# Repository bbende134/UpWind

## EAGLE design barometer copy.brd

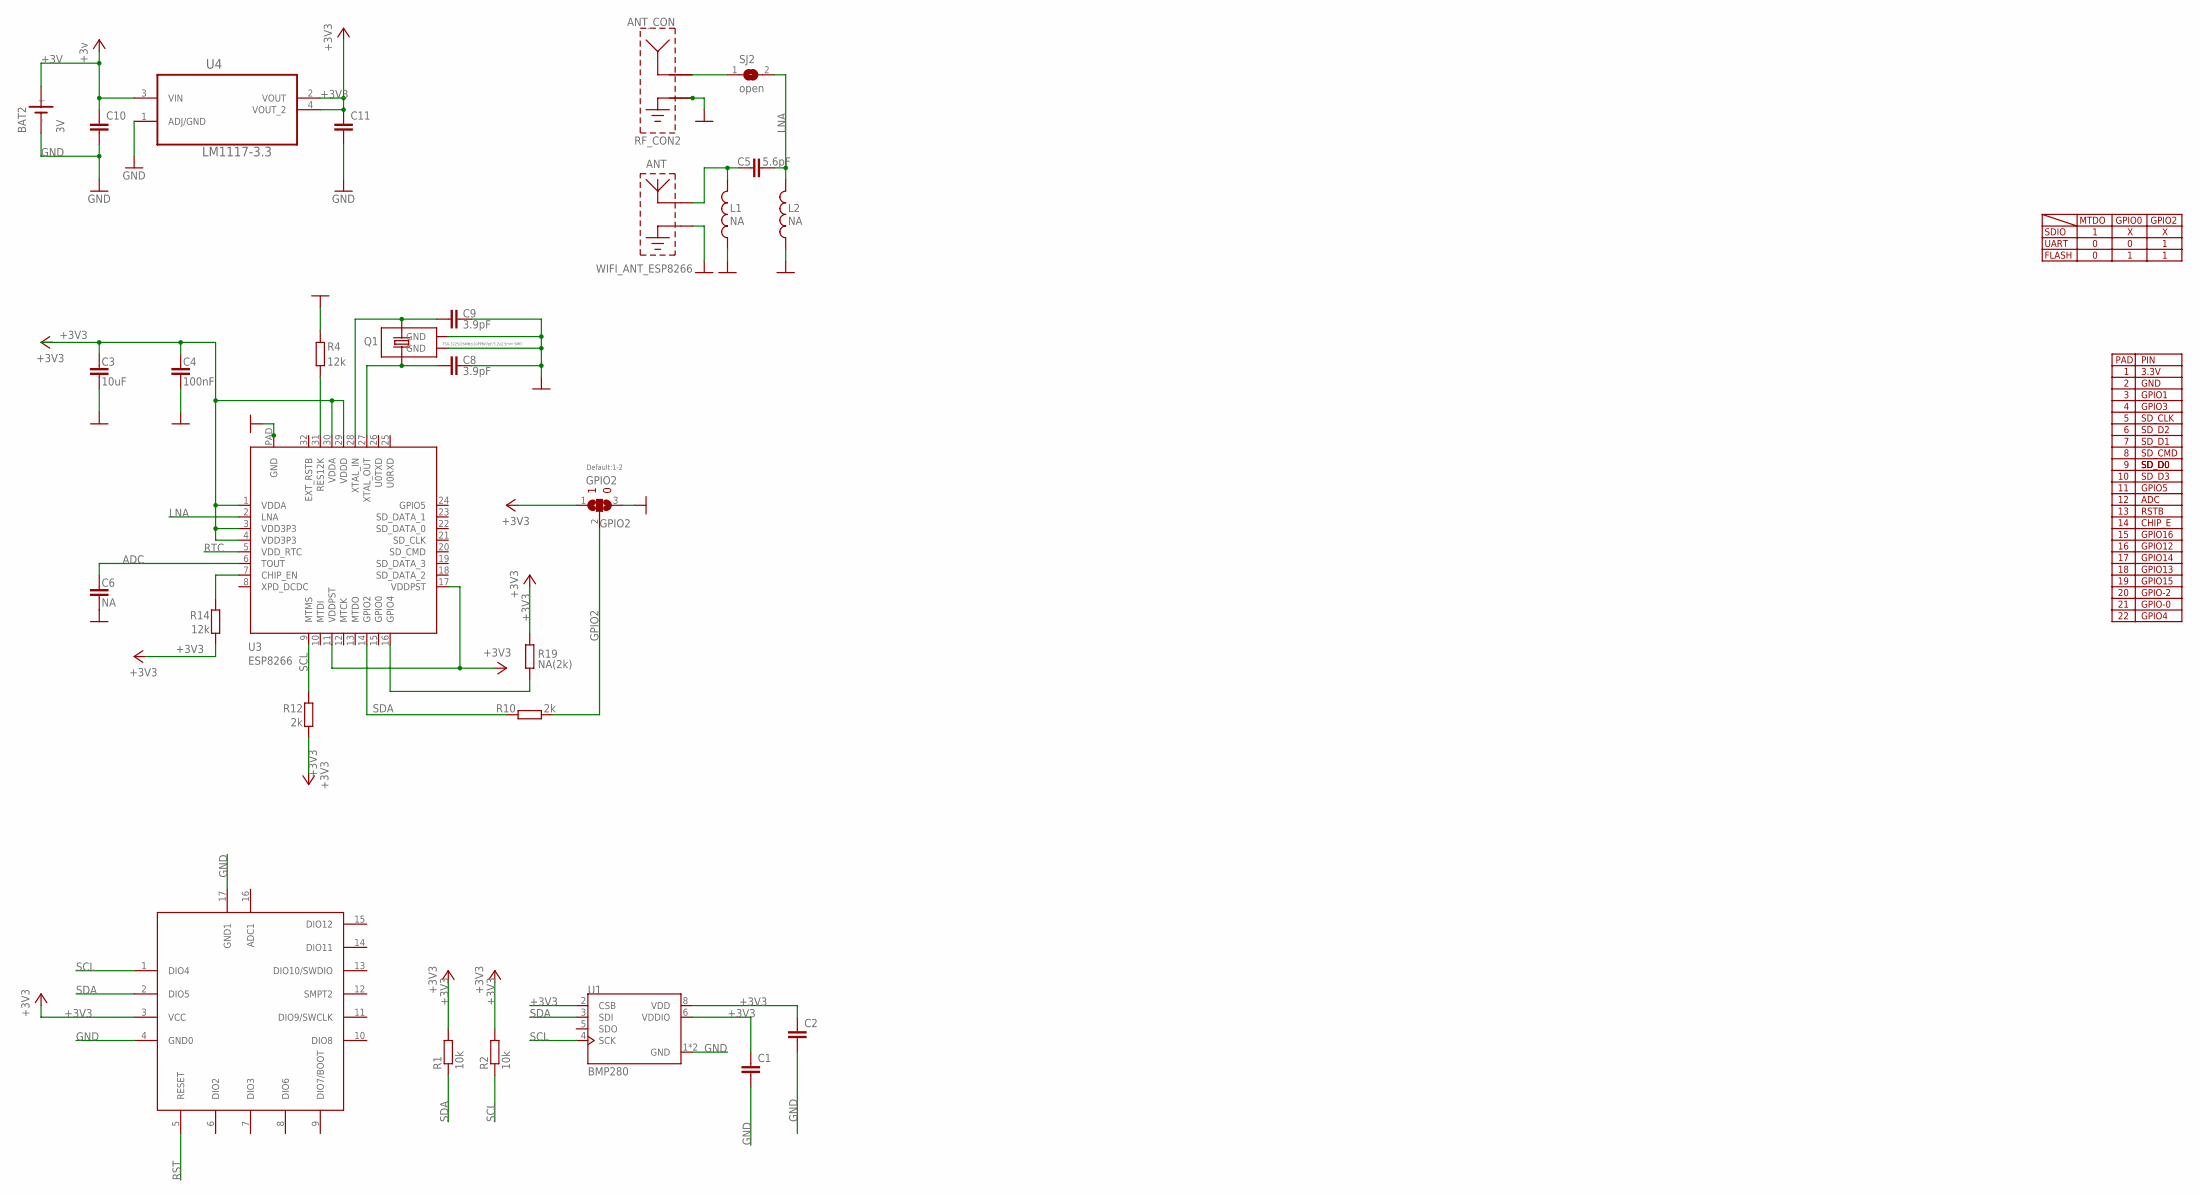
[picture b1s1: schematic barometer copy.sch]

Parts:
ANT: WIFI_ANT_ESP8266; ESP8266_ANT
ANT_CON: RF_CON2; RF_CONNECTOR_I-PEX_NO_CREAM
BAT2: 3V; SN2032
C1, C2, C10: 47u; C1206
C3: 10uF; C0603_DWS
C4: 100nF; C0402_TI
C5: 5.6pF; C0402_TI
C6: NA; C0402_TI
C8, C9: 3.9pF; C0402_TI
C11: 10u; C1206
GPIO2: Default:1-2; SJ_2_SMALLER
L1, L2: NA; L0402_TI
Q1: TSX-3225/26MHz/10PPM/7pF/3.2x2.5mm SMD; NX3225SA
R1, R2: 10k; R0402
R4, R14: 12k; R0402_TI
R10, R12: 2k; R0402_TI
R19: NA(2k); R0402_TI
SJ2: open; SJ_1_SMALLER
U1: BMP280; XDCR_BMP280
U3: ESP8266; QFN32_PAD
U4: LM1117-3.3; SOT230
U$1: BLUENRG-234BLEMODULE

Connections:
+3V: BAT2.+, C10.1, U4.3 (VIN)
+3V3: C1.1, C2.1, C3.1, C4.1, C11.1, GPIO2.1, R1.2, R2.2, R12.2, R14.2, R19.1, U1.2 (CSB), U1.6 (VDDIO), U1.8 (VDD), U3.1 (VDDA), U3.3 (VDD3P3), U3.4 (VDD3P3), U3.11 (VDDPST), U3.17 (VDDPST), U3.29 (VDDD), U3.30 (VDDA), U4.2 (VOUT), U4.4 (VOUT_2), U$1.3 (VCC)
ADC: C6.1, U3.6 (TOUT)
GND: ANT.GND, ANT_CON.1 (GND_1), ANT_CON.2 (GND_2), BAT2.-, C1.2, C2.2, C3.2, C4.2, C6.2, C8.1, C9.1, C10.2, C11.2, GPIO2.3, L1.1, L2.1, Q1.NC_1 (GND), Q1.NC_2 (GND), R4.2, U1.1 (GND), U1.7 (GND), U3.P$1 (GND), U3.P$2 (GND), U3.P$3 (GND), U3.P$4 (GND), U3.P$5 (GND), U3.P$6 (GND), U3.P$7 (GND), U3.P$8 (GND), U3.P$9 (GND), U3.PAD (GND), U4.1 (ADJ/GND), U$1.4 (GND0), U$1.17 (GND1)
GPIO2: GPIO2.2, R10.1
GPIO4: R19.2, U3.16 (GPIO4)
LNA: C5.2, L2.2, SJ2.2, U3.2 (LNA)
unnamed: ANT_CON.ANT, SJ2.1
unnamed: R14.1, U3.7 (CHIP_EN)
unnamed: ANT.ANT, C5.1, L1.2
unnamed: C8.2, Q1.2, U3.27 (XTAL_OUT)
unnamed: R4.1, U3.31 (RES12K)
unnamed: C9.2, Q1.1, U3.28 (XTAL_IN)
RST: U$1.5 (RESET)
RTC: U3.5 (VDD_RTC)
SCL: R2.1, R12.1, U1.4 (SCK), U3.9 (MTMS), U$1.1 (DIO4)
SDA: R1.1, R10.2, U1.3 (SDI), U3.14 (GPIO2), U$1.2 (DIO5)

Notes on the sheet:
SDIO
UART
FLASH
MTDO
GPIO0
GPIO2
PAD
GPIO1
GPIO3
SD_CLK
SD_D0
SD_D1
SD_D2
SD_D3
SD_CMD
3.3V
GND
GPIO5
GPIO4
GPIO-0
GPIO-2
GPIO15
GPIO13
GPIO12
GPIO14
GPIO16
ADC
PIN
RSTB
CHIP_E

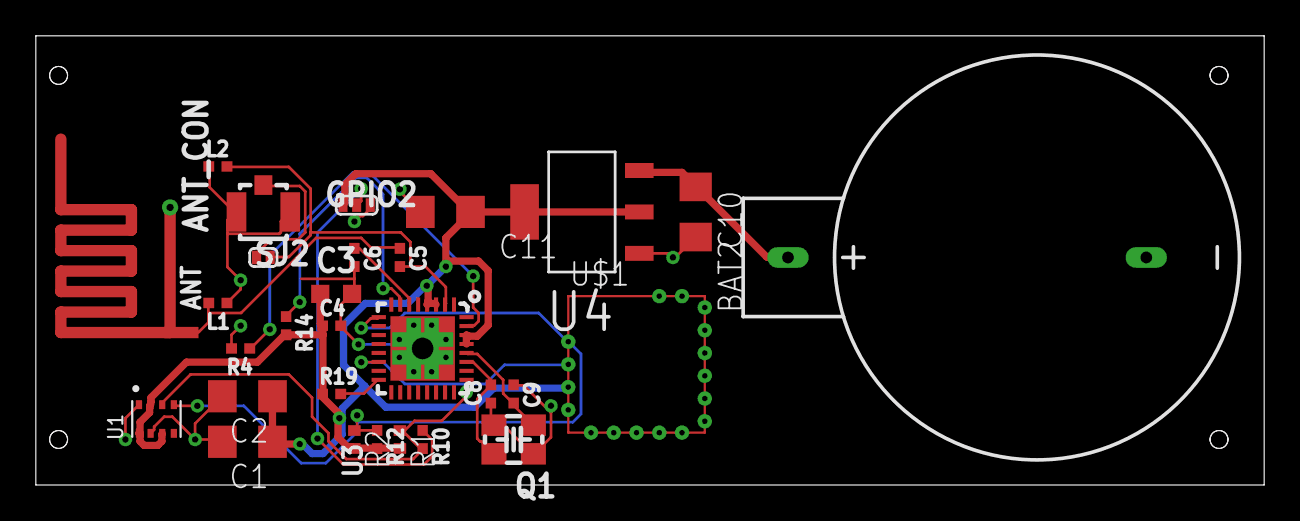
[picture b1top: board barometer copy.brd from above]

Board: 2 copper layers, 68.6 x 25.1 mm, 29 parts (0 on the bottom side), 15 nets.

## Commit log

2022-11-01 PCBs
2022-11-01 svg and docu
2022-11-01 One pager
2022-11-01 AR design
